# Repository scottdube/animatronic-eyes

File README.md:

# animatronic-eyes

A build of Will Cogley's **Basic EyeMech** (Nilheim Mechatronics): two eyes,
each moving on X and Y, plus four eyelids. Six SG90 servos run from an Adafruit
PCA9685 driver on an ESP32, and a PS4 (DualShock 4) controller drives it over
Bluetooth.

## Credit and license

The mechanism, the printable parts and the original Arduino sketch are
**Will Cogley's** work, published as the
[Simple Eye Mechanism (Basic EyeMech)](https://willcogley.notion.site/Simple-Eye-Mechanism-983e6cad7059410d9cb958e8c1c5b700)
under [CC BY-NC-SA 4.0](https://creativecommons.org/licenses/by-nc-sa/4.0/).
His original license notice is kept in `reference/License.html` and
`hardware/kit-stl/License.html`. For commercial use of his design, contact him
as that notice says. This repository cannot grant it.

Everything here is an adaptation of that kit or is built to go with it, so the
**whole repository is released under the same license, CC BY-NC-SA 4.0** (full
text in `LICENSE`). You may share and adapt it with attribution, for
non-commercial purposes only, and must release your changes under the same
license.

## What is his, and what changed

| Path | What it is | Relation to the kit |
|---|---|---|
| `hardware/kit-stl/` | The 15 printable STLs, `Complete Model.stl` and the license | **His files, unmodified** (kit downloaded May 2024) |
| `firmware/Low_Tier_Code/` | The kit's Arduino sketch | **His code**, plus three debug `Serial.println` lines |
| `reference/` | Kit images and license | **His**, unmodified |
| `hardware/kit-f3d/` | The 15 STLs converted to Fusion designs (faceted), plus the conversion script | Format conversion of his parts |
| `hardware/native/` | Every kit part rebuilt as parametric Fusion features, within 0.002 mm of his STL, plus SG90 models and an assembly | Adaptation of his parts |
| `firmware/Low_Tier_Code_mod_ps4/` | First PS4-controller version of his sketch (2024) | Adaptation of his code |
| `firmware/EyeMech_PS4/` | Current firmware: PS4 control, a web settings page with live sliders, Wi-Fi OTA updates and autonomous "scenes". His servo math is kept unchanged. | Adaptation of his code |
| `firmware/pca_bench_test/` | Bench test for the PCA9685 board | New |
| `hardware/carrier/`, `hardware/fitcheck/` | KiCad carrier board for the ESP32 and PCA9685, with print-to-check templates | New |
| `tools/meshcad/` | Mesh and CAD helper scripts | New |
| `docs/` | Build notes: CAD write-ups, board photos, traps | New |

## Building the firmware

Copy `firmware/EyeMech_PS4/secrets.h.template` to `secrets.h` and fill in your
Wi-Fi details (that file is ignored by git). Then:

```bash
./build.sh            # compile only
./build.sh usb        # compile and flash over USB
./build.sh ota HOST   # compile and flash over Wi-Fi
```

`build.sh` uses the arduino-cli bundled with Arduino IDE 2 on macOS, and the
`min_spiffs` partition scheme so that OTA has two app slots. It needs the
ESP32 Arduino core, the Adafruit PWM Servo Driver library and
[PS4Controller](https://github.com/pablomarquez76/PS4_Controller_Host).

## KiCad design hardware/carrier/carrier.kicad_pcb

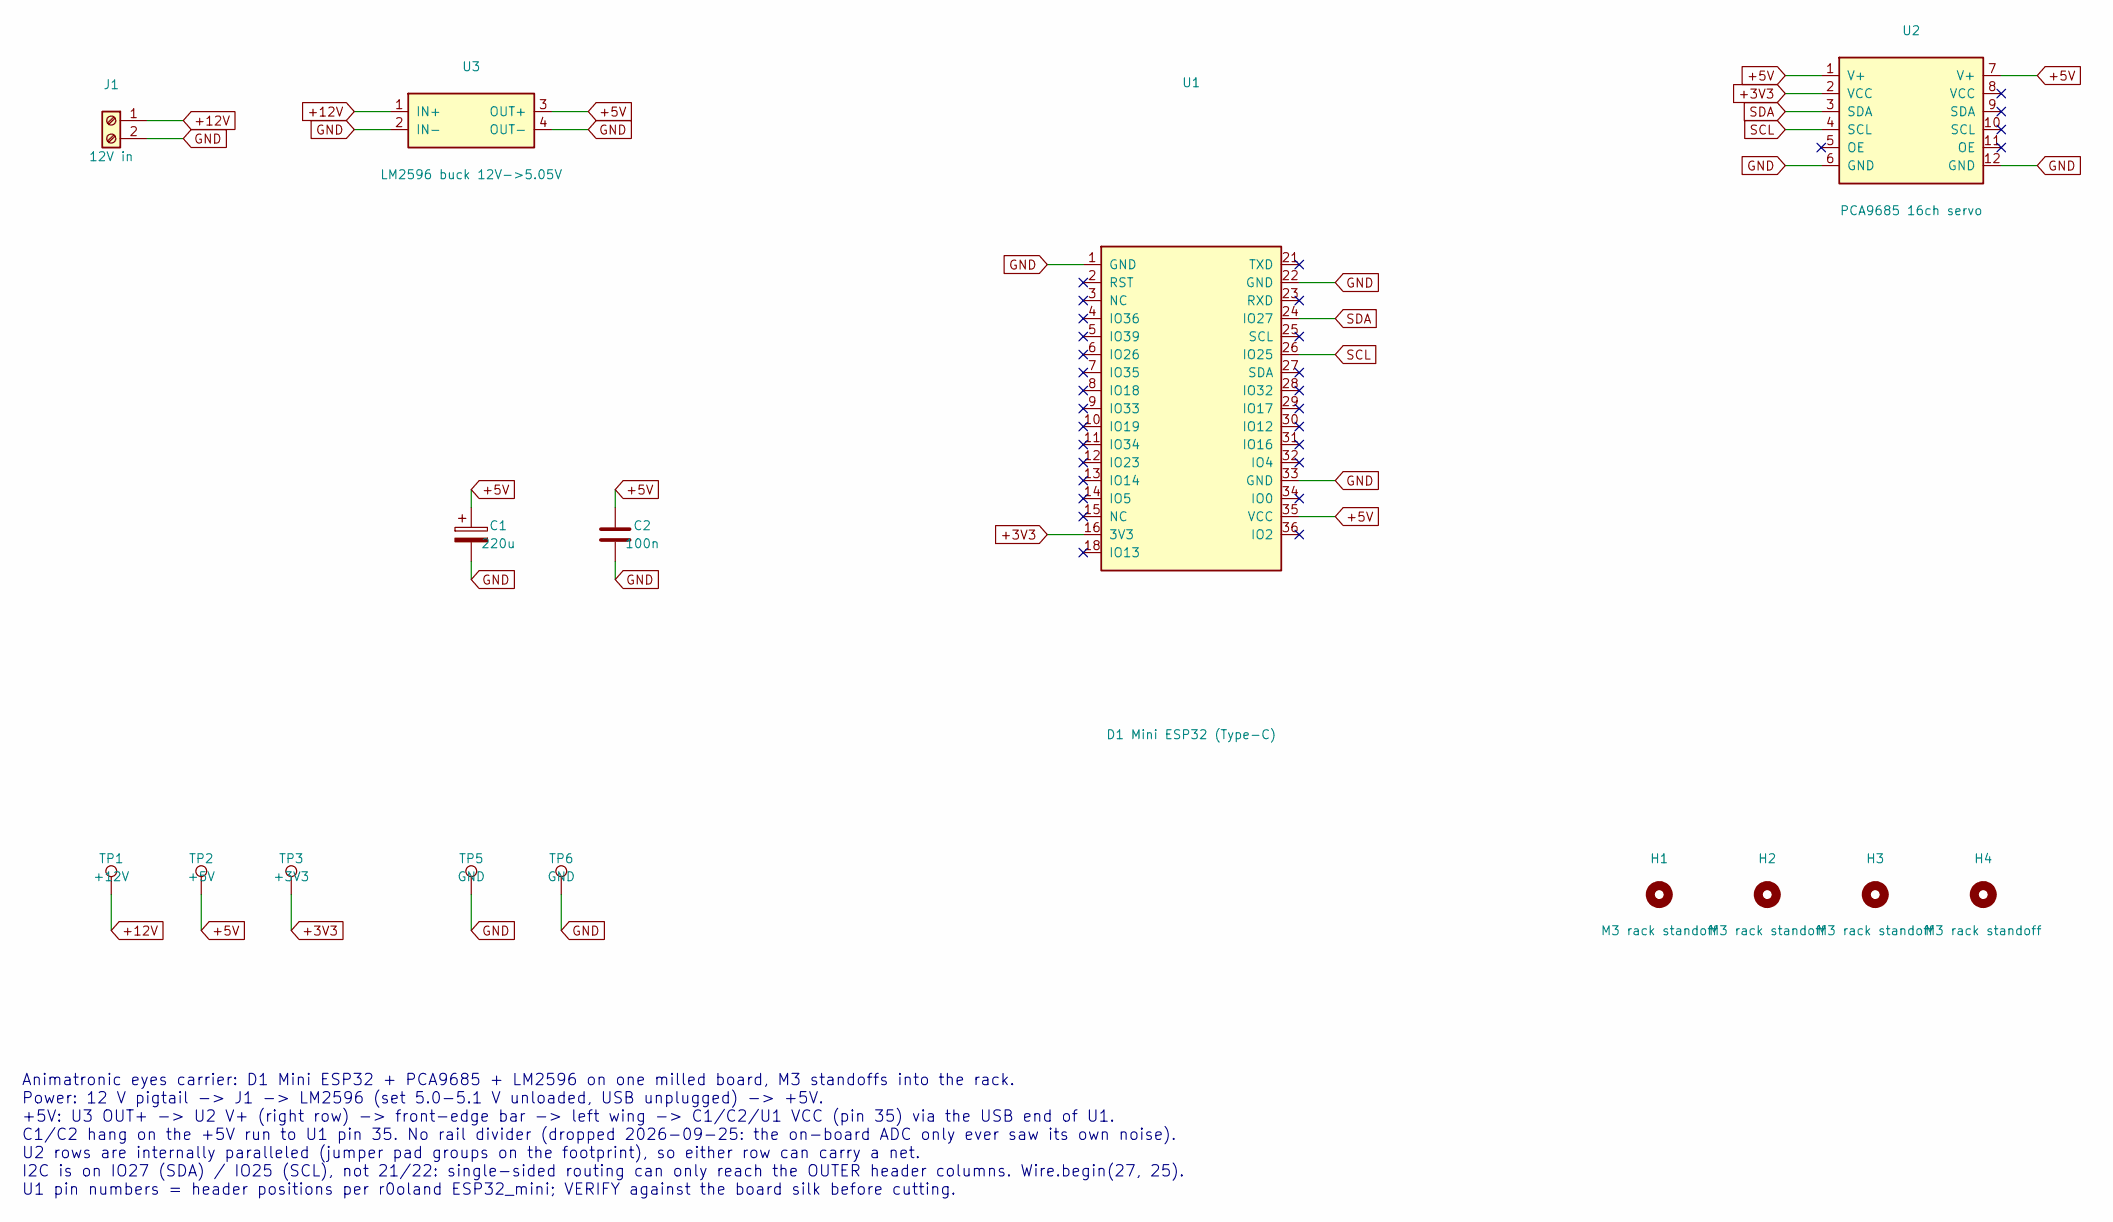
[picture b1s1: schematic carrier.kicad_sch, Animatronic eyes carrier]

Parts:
C1: 220u; CP_Radial_D6.3_P2.5
C2: 100n; C_Disc_P5.08
H1, H2, H3, H4: M3 rack standoff; MountingHole_M3_3.175
J1: 12V in; KF301_1x02_P5.08
TP1: +12V; TestPoint_THT_D2.2_1.181
TP2: +5V; TestPoint_THT_D2.2_1.181
TP3: +3V3; TestPoint_THT_D2.2_1.181
TP5, TP6: GND; TestPoint_THT_D2.2_1.181
U1: D1 Mini ESP32 (Type-C); D1_Mini_ESP32_THT
U2: PCA9685 16ch servo; PCA9685_Adafruit_Module
U3: LM2596 buck 12V->5.05V; LM2596_Module

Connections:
+3V3: TP3.1, U1.16 (3V3), U2.2 (VCC)
+5V: C1.1, C2.1, TP2.1, U1.35 (VCC), U2.1 (V+), U2.7 (V+), U3.3 (OUT+)
+12V: J1.1, TP1.1, U3.1 (IN+)
GND: C1.2, C2.2, J1.2, TP5.1, TP6.1, U1.1 (GND), U1.22 (GND), U1.33 (GND), U2.6 (GND), U2.12 (GND), U3.2 (IN-), U3.4 (OUT-)
SCL: U1.26 (IO25), U2.4 (SCL)
SDA: U1.24 (IO27), U2.3 (SDA)

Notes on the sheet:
Animatronic eyes carrier: D1 Mini ESP32 + PCA9685 + LM2596 on one milled board, M3 standoffs into the rack. Power: 12 V pigtail -> J1 -> LM2596 (set 5.0-5.1 V unloaded, USB unplugged) -> +5V. +5V: U3 OUT+ -> U2 V+ (right row) -> front-edge bar -> left wing -> C1/C2/U1 VCC (pin 35) via the USB end o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

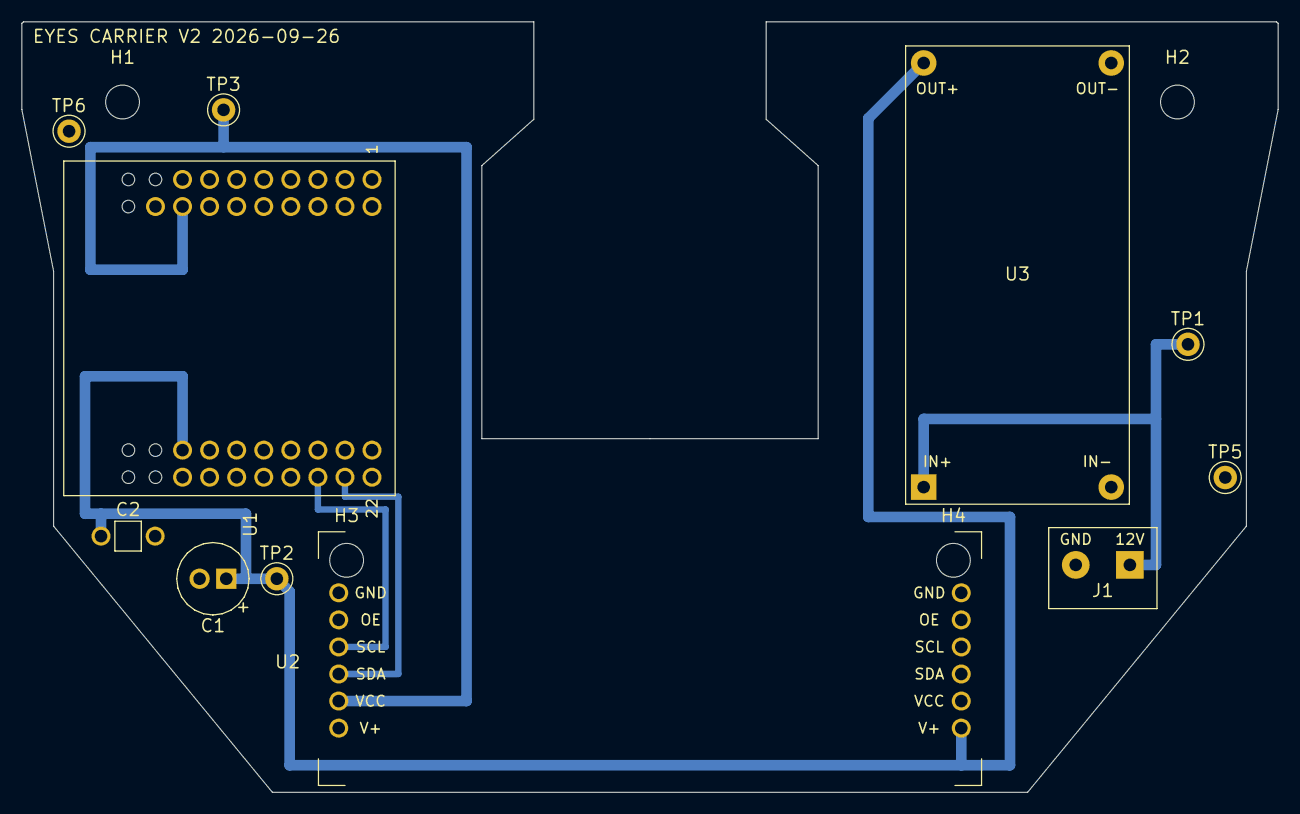
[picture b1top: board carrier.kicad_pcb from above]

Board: 2 copper layers, 117.9 x 72.3 mm, 15 parts (0 on the bottom side), 6 nets.
